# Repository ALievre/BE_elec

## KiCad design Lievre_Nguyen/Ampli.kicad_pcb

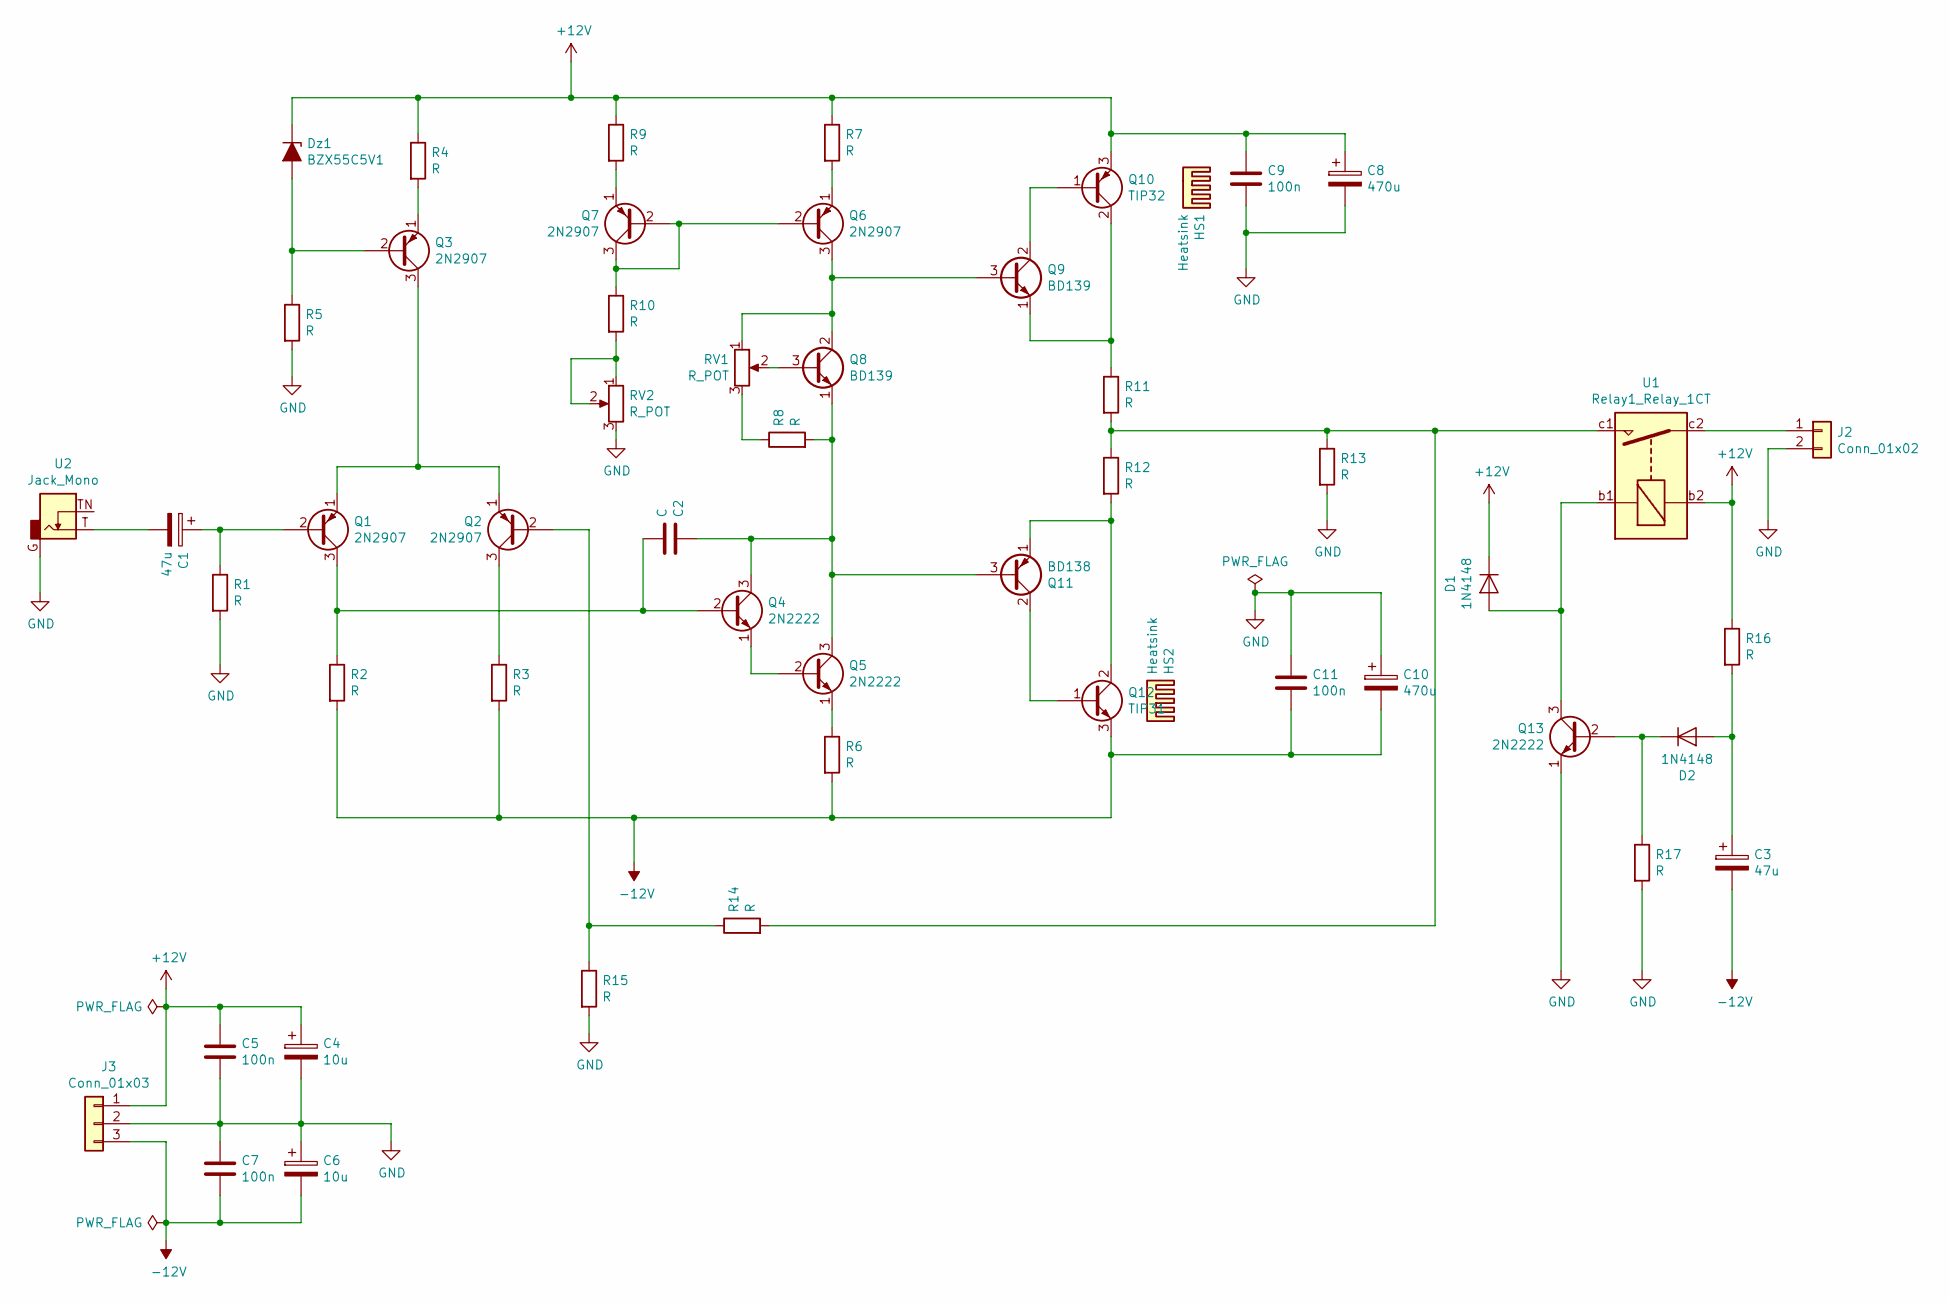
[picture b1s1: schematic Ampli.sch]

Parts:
C1, C3: 47u; CP_Radial_D8.0mm_P5.00mm
C2: C; C_Rect_L7.2mm_W3.5mm_P5.00mm_FKS2_FKP2_MKS2_MKP2
C4, C6: 10u; CP_Radial_D8.0mm_P5.00mm
C5, C7, C9, C11: 100n; C_Rect_L7.2mm_W3.5mm_P5.00mm_FKS2_FKP2_MKS2_MKP2
C8, C10: 470u; CP_Radial_D12.5mm_P5.00mm
D1, D2: 1N4148; D_DO-35_SOD27_P7.62mm_Horizontal
Dz1: BZX55C5V1; D_DO-35_SOD27_P10.16mm_Horizontal
HS1, HS2: Heatsink; Heatsink_Fischer_SK104-STC-STIC_35x13mm_2xDrill2.5mm
J2: Conn_01x02; PhoenixContact_MSTBVA_2,5_2-G-5,08_1x02_P5.08mm_Vertical
J3: Conn_01x03; PhoenixContact_MSTBVA_2,5_3-G-5,08_1x03_P5.08mm_Vertical
Q1, Q2, Q3, Q6, Q7: 2N2907; TO-18-3
Q4, Q5, Q13: 2N2222; TO-18-3
Q8, Q9: BD139; TO-126-3_Vertical
Q10: TIP32; TO-220-3_Vertical
Q11: BD138; TO-126-3_Vertical
Q12: TIP31; TO-220-3_Vertical
R1, R2, R3, R4, R5, R6, R7, R8, R9, R10, R13, R14, R15, R16, R17: R; R_Axial_DIN0207_L6.3mm_D2.5mm_P10.16mm_Horizontal
R11, R12: R; R_Axial_DIN0516_L15.5mm_D5.0mm_P20.32mm_Horizontal
RV1, RV2: R_POT; Potentiometer_Bourns_3296W_Vertical
U1: Relay1_Relay_1CT; Relais_112LMH2
U2: Jack_Mono; Jack_35RAPC2AV

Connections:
+12V: C4.1, C5.1, C8.1, C9.1, D1.1 (K), Dz1.1 (K), J3.1, Q10.3 (E), R4.1, R7.1, R9.1, R16.1, U1.b2
-12V: C3.2, C6.2, C7.2, C10.2, C11.2, J3.3, Q12.3 (E), R2.2, R3.2, R6.2
GND: C4.2, C5.2, C6.1, C7.1, C8.2, C9.2, C10.1, C11.1, J2.2, J3.2, Q13.1 (E), R1.2, R5.2, R13.2, R15.2, R17.2, RV2.3, U2.G
unnamed: C1.1, Q1.2 (B), R1.1
unnamed: C1.2, U2.T
unnamed: C2.1, Q4.3 (C), Q5.3 (C), Q8.1 (E), Q11.3 (B), R8.2
unnamed: C2.2, Q1.3 (C), Q4.2 (B), R2.1
unnamed: C3.1, D2.2 (A), R16.2
unnamed: D1.2 (A), Q13.3 (C), U1.b1
unnamed: D2.1 (K), Q13.2 (B), R17.1
unnamed: Dz1.2 (A), Q3.2 (B), R5.1
unnamed: J2.1, U1.c2
unnamed: Q1.1 (E), Q2.1 (E), Q3.3 (C)
unnamed: Q2.2 (B), R14.1, R15.1
unnamed: Q2.3 (C), R3.1
unnamed: Q3.1 (E), R4.2
unnamed: Q4.1 (E), Q5.2 (B)
unnamed: Q5.1 (E), R6.1
unnamed: Q6.1 (E), R7.2
unnamed: Q6.2 (B), Q7.2 (B), Q7.3 (C), R10.1
unnamed: Q6.3 (C), Q8.2 (C), Q9.3 (B), RV1.1
unnamed: Q7.1 (E), R9.2
unnamed: Q8.3 (B), RV1.2
unnamed: Q9.2 (C), Q10.1 (B)
unnamed: Q9.1 (E), Q10.2 (C), R11.1
unnamed: Q11.1 (E), Q12.2 (C), R12.2
unnamed: Q11.2 (C), Q12.1 (B)
unnamed: R8.1, RV1.3
unnamed: R10.2, RV2.1, RV2.2
unnamed: R11.2, R12.1, R13.1, R14.2, U1.c1

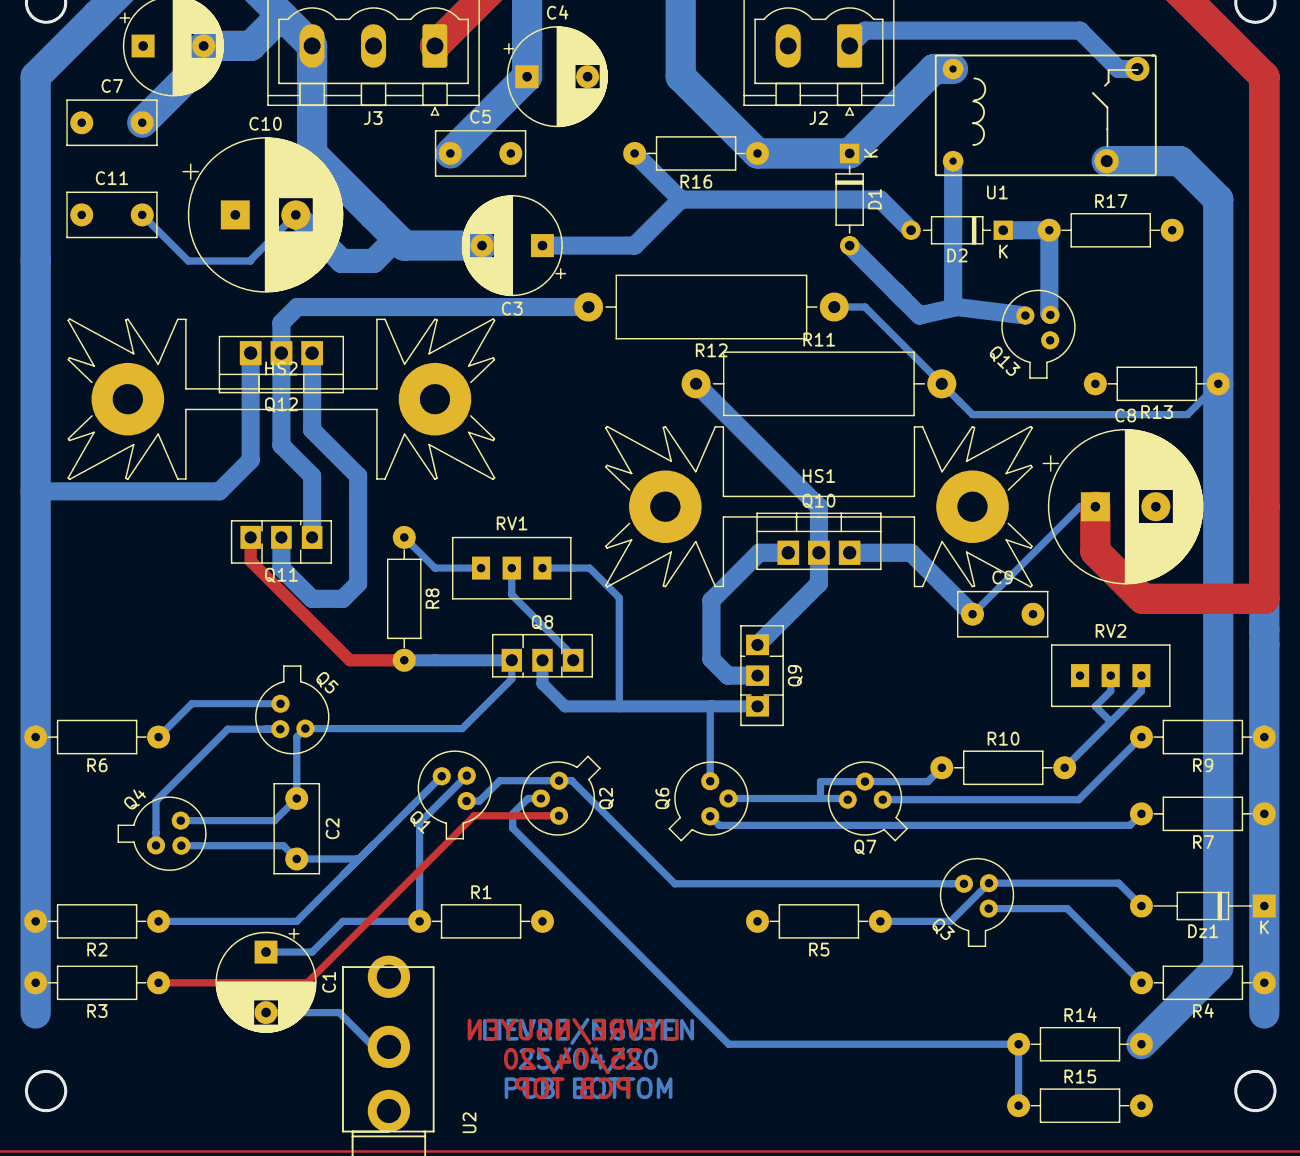
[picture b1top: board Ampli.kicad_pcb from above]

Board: 2 copper layers, 52 parts (0 on the bottom side), 30 nets.

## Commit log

2020-03-22 Added source files
    - Added lib along with modifications
    - Added project work so far
2020-03-24 Fin de l'étape 'Saisie du schéma' - réalisation de l'empreinte du relay - numérotation des composants - vérifiaction ERC - association des empreintes - génération de la netlist
2020-03-24 Début de l'étape Routage - added page settings du routeur - added page settings du schéma - added DRC - added Design rules - imported the netlist
2020-04-25 Fin du placement Plus de problème de relay
2020-04-25 Fin du routage
2020-04-27 Fin du routage Résolution de quelques petites erreurs
2020-05-14 Correction des erreurs sauf erreur 'bornier d'enceinte (sortie)'
